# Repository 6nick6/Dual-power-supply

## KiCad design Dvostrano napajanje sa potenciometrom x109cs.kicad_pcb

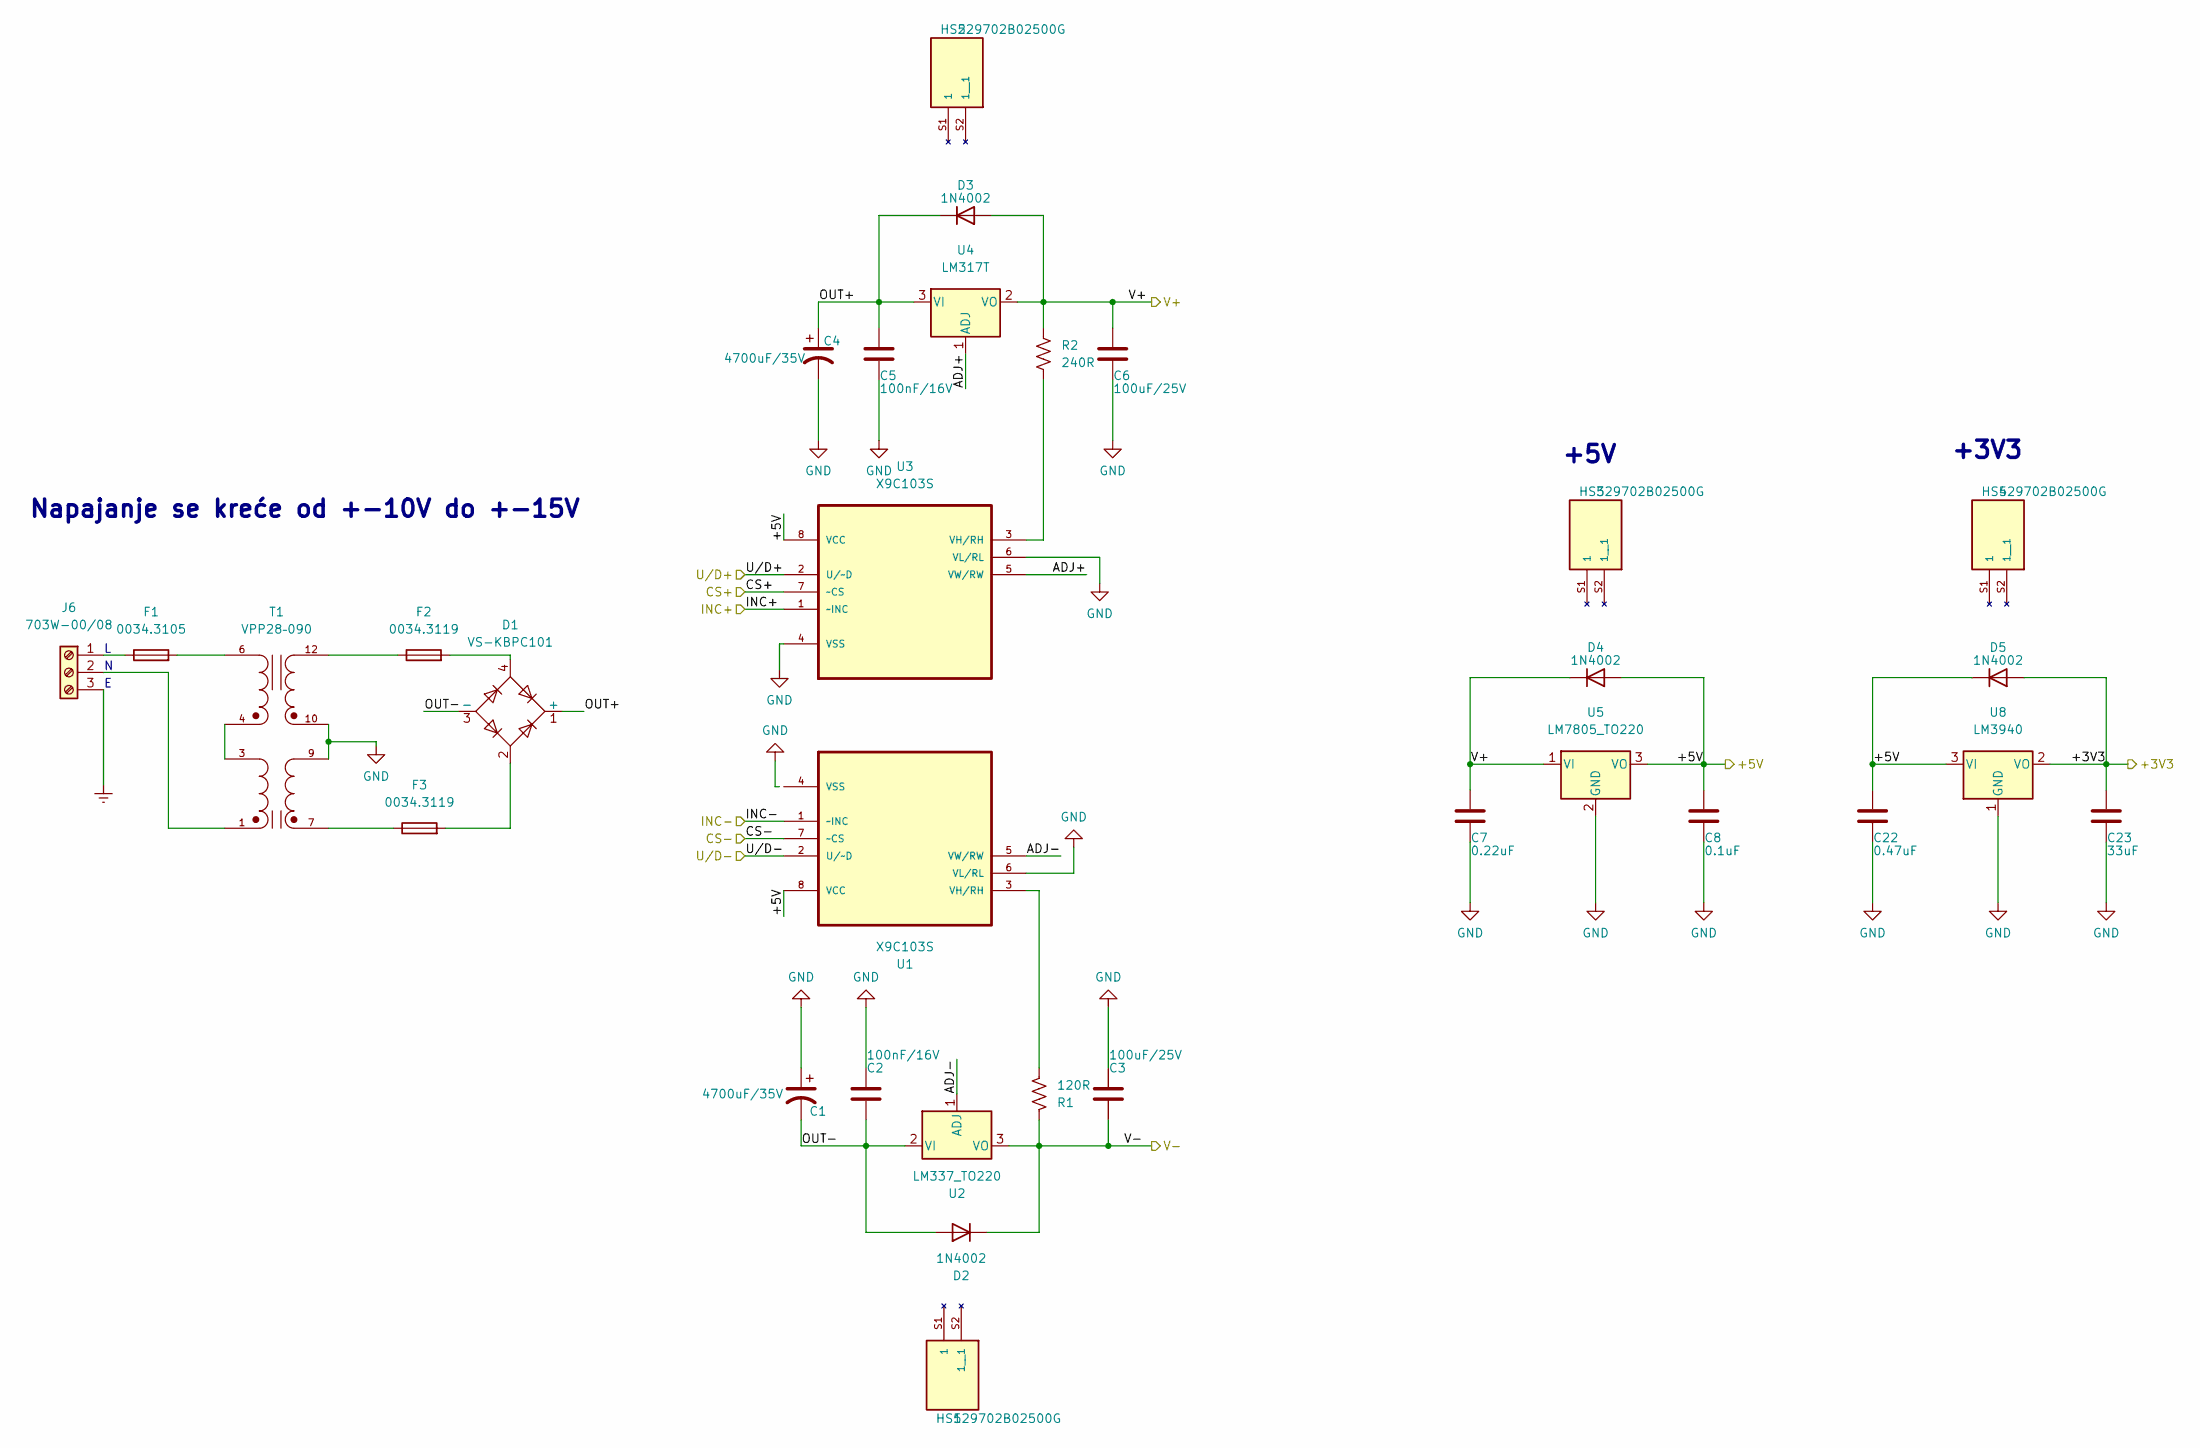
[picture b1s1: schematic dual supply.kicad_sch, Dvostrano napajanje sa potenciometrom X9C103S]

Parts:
C1, C4: 4700uF/35V; CAPPRD750W80D1800H4200
C2, C5: 100nF/16V; C_0805_2012Metric
C3, C6: 100uF/25V; C_0805_2012Metric
C7: 0.22uF; C_0805_2012Metric
C8: 0.1uF; C_0805_2012Metric
C22: 0.47uF; C_0805_2012Metric
C23: 33uF; C_0805_2012Metric
D1: VS-KBPC101; Diode_Bridge_Vishay_KBPC1
D2, D3, D4, D5: 1N4002; D_DO-41_SOD81_P10.16mm_Horizontal
F1: 0034.3105; Fuseholder_Cylinder-5x20mm_Schurter_0031_8201_Horizontal_Op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
F2, F3: 0034.3119; Fuseholder_Cylinder-5x20mm_Schurter_0031_8201_Horizontal_Op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
HS1, HS2, HS3, HS4: 529702B02500G; HSINK_529702B02500G
J6: 703W-00/08; TerminalBlock_Phoenix_MKDS-1,5-3_1x03_P5.00mm_Horizontal
R1: 120R; C_0805_2012Metric
R2: 240R; C_0805_2012Metric
T1: VPP28–090; XFMR_VPP28-090
U1, U3: X9C103S; SOIC127P600X175-8N; MPN X9C103S
U2: LM337_TO220; TO-220-3_Vertical
U4: LM317T; TO-220-3_Vertical
U5: LM7805_TO220; TO-220-3_Vertical
U8: LM3940; TO-220-3_Vertical

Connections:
/+3V3: C23.1, D5.2 (A), U8.2 (VO); also elsewhere on the board
/+5V: C8.1, C22.1, D4.2 (A), D5.1 (K), U1.8 (VCC), U3.8 (VCC), U5.3 (VO), U8.3 (VI); also elsewhere on the board
/CS+: U3.7 (~CS); also elsewhere on the board
/CS-: U1.7 (~CS); also elsewhere on the board
/Dual supply/ADJ+: U3.5 (VW/RW), U4.1 (ADJ)
/Dual supply/ADJ-: U1.5 (VW/RW), U2.1 (ADJ)
/Dual supply/OUT+: C4.1, C5.1, D1.1 (+), D3.1 (K), U4.3 (VI)
/Dual supply/OUT-: C1.2, C2.1, D1.3 (-), D2.2 (A), U2.2 (VI)
/INC+: U3.1 (~INC); also elsewhere on the board
/INC-: U1.1 (~INC); also elsewhere on the board
/U/D+: U3.2 (U/~D); also elsewhere on the board
/U/D-: U1.2 (U/~D); also elsewhere on the board
/V+: C6.1, C7.1, D3.2 (A), D4.1 (K), R2.1, U4.2 (VO), U5.1 (VI); also elsewhere on the board
/V-: C3.1, D2.1 (K), R1.1, U2.3 (VO); also elsewhere on the board
Earth: J6.3
GND: C1.1, C2.2, C3.2, C4.2, C5.2, C6.2, C7.2, C8.2, C22.2, C23.2, T1.9, T1.10, U1.6 (VL/RL), U3.4 (VSS), U3.6 (VL/RL), U5.2 (GND), U8.1 (GND); also elsewhere on the board
unnamed: D1.2, F3.2
unnamed: D1.4, F2.2
unnamed: F1.1, J6.1
unnamed: F1.2, T1.6
unnamed: F2.1, T1.12
unnamed: F3.1, T1.7
unnamed: J6.2, T1.1
unnamed: R1.2, U1.3 (VH/RH)
unnamed: R2.2, U3.3 (VH/RH)
unnamed: T1.3, T1.4

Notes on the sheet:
+3V3
+5V
Napajanje se kreće od +-10V do +-15V

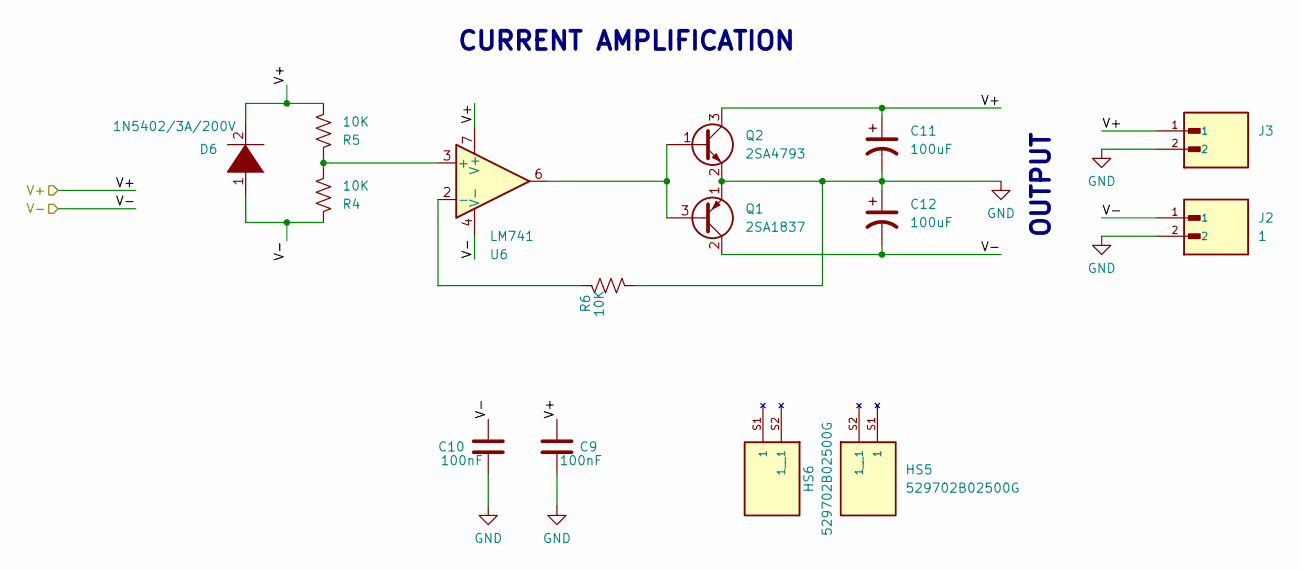
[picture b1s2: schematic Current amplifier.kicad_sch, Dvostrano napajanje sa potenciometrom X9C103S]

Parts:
C9, C10: 100nF; CAPC2012X70
C11, C12: 100uF; CP_Radial_D7.5mm_P2.50mm
D6: 1N5402/3A/200V; D_DO-201AD_P15.24mm_Horizontal
HS5, HS6: 529702B02500G; HSINK_529702B02500G
J2, J3: 1; TerminalBlock_Phoenix_MKDS-1,5-2_1x02_P5.00mm_Horizontal; PARTREV 11.03.2024
Q1: 2SA1837; TO-220-3_Vertical
Q2: 2SA4793; TO-220-3_Vertical
R4, R5, R6: 10K; R_0805_2012Metric
U6: LM741; DIP-8_W7.62mm

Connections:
/V+: C9.1, C11.1, D6.2 (A), J3.1, Q2.3 (C), R5.2, U6.7 (V+); also elsewhere on the board
/V-: C10.1, C12.2, D6.1 (K), J2.1, Q1.2 (C), R4.1, U6.4 (V-); also elsewhere on the board
GND: C9.2, C10.2, C11.2, C12.1, J2.2, J3.2, Q1.1 (E), Q2.2 (E), R6.2; also elsewhere on the board
unnamed: Q1.3 (B), Q2.1 (B), U6.6
unnamed: R4.2, R5.1, U6.3 (+)
unnamed: R6.1, U6.2 (-)

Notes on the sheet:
CURRENT AMPLIFICATION
OUTPUT

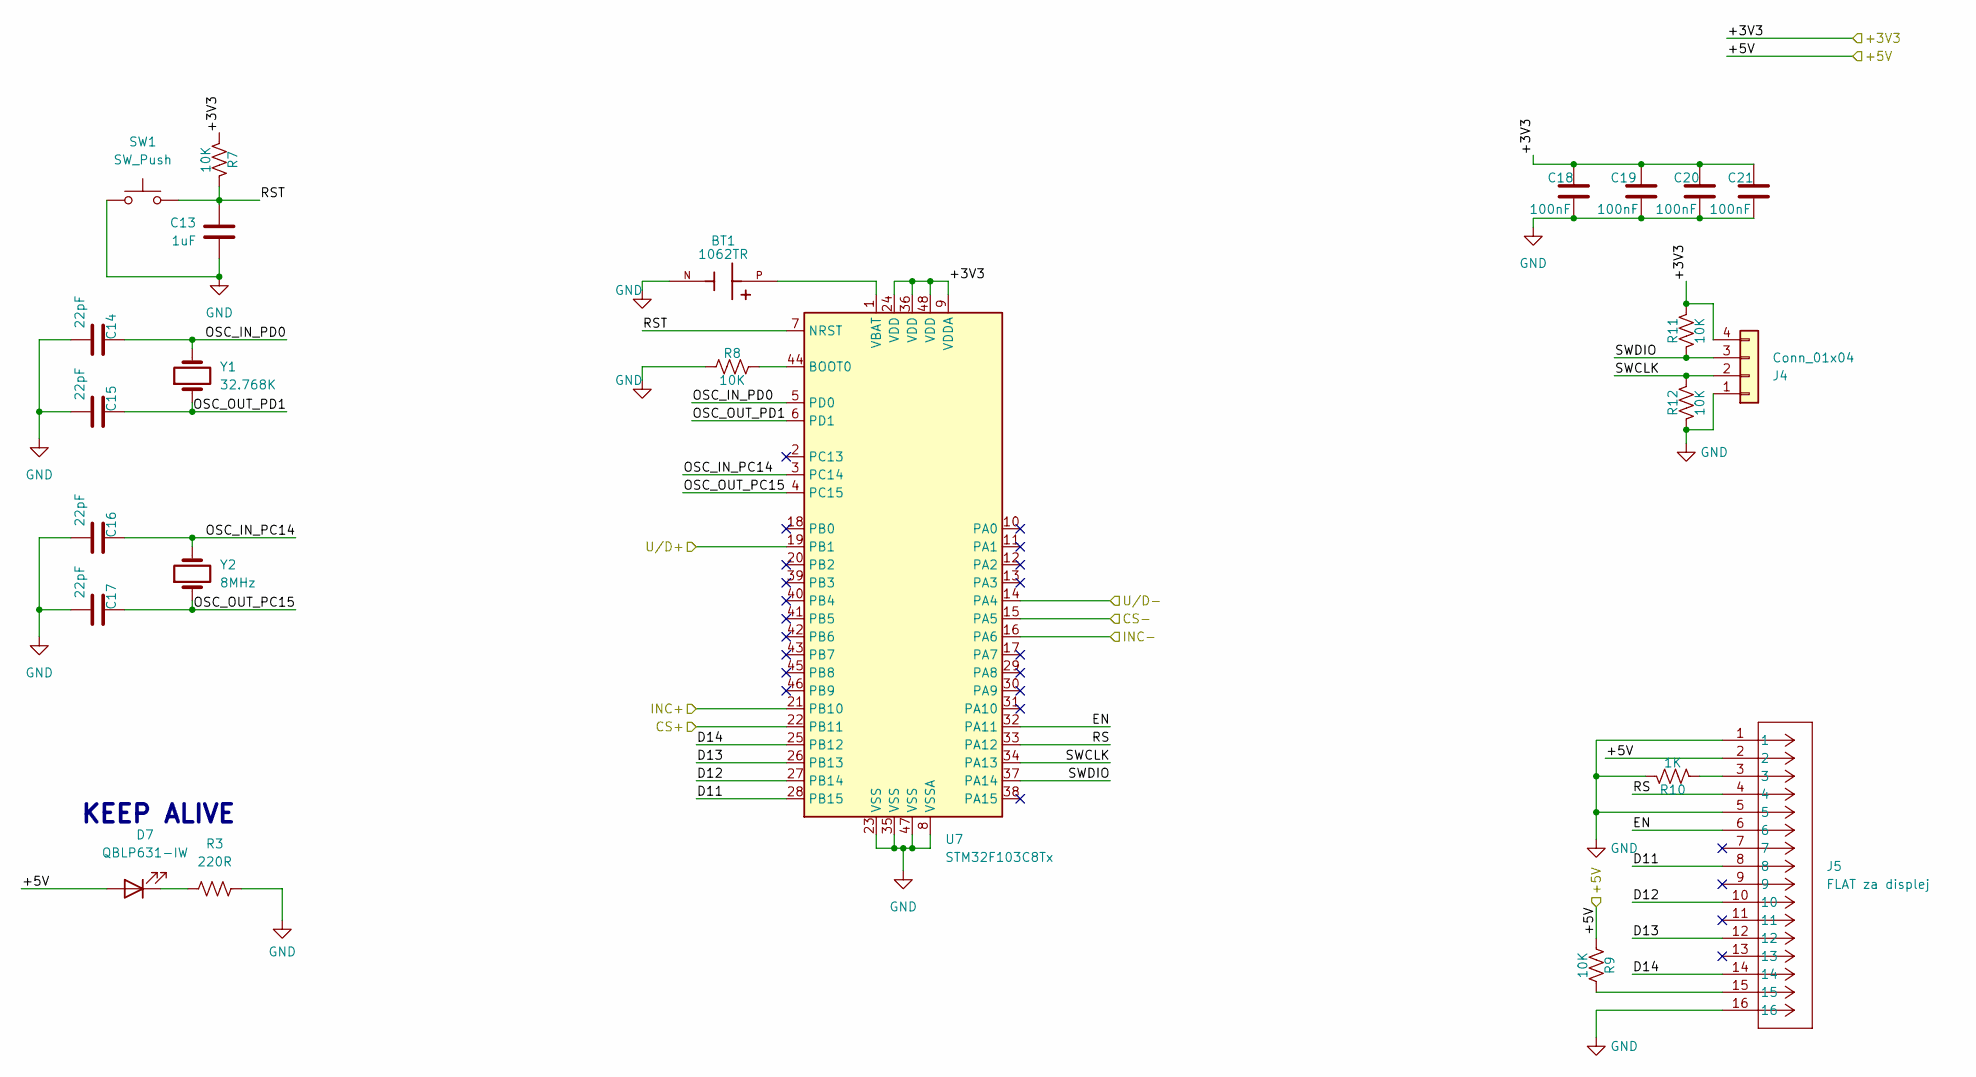
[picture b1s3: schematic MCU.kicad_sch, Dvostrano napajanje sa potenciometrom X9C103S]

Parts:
BT1: 1062TR; BAT_1062TR; PARTREV F
C13: 1uF; C_0805_2012Metric
C14, C15, C16, C17: 22pF; C_0805_2012Metric
C18, C19, C20, C21: 100nF; C_0805_2012Metric
D7: QBLP631-IW; LED_0805_2012Metric
J4: Conn_01x04; PinHeader_1x04_P2.54mm_Vertical
J5: FLAT za displej; CONN_XG4A-1631_OMR
R3: 220R; R_0805_2012Metric
R7, R8, R9, R11, R12: 10K; R_0805_2012Metric
R10: 1K; R_0805_2012Metric
SW1: SW_Push; SW_Tactile_SPST_NO_Straight_CK_PTS636Sx25SMTRLFS
U7: STM32F103C8Tx; LQFP-48_7x7mm_P0.5mm
Y1: 32.768K; Crystal_C26-LF_D2.1mm_L6.5mm_Vertical
Y2: 8MHz; Resonator-2Pin_W10.0mm_H5.0mm

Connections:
/+3V3: C18.1, C19.1, C20.1, C21.1, J4.4, R7.2, R11.1, U7.9 (VDDA), U7.24 (VDD), U7.36 (VDD), U7.48 (VDD); also elsewhere on the board
/+5V: D7.2 (A), J5.2, R9.1; also elsewhere on the board
/CS+: U7.22 (PB11); also elsewhere on the board
/CS-: U7.15 (PA5); also elsewhere on the board
/INC+: U7.21 (PB10); also elsewhere on the board
/INC-: U7.16 (PA6); also elsewhere on the board
/MCU/D11: J5.8, U7.28 (PB15)
/MCU/D12: J5.10, U7.27 (PB14)
/MCU/D13: J5.12, U7.26 (PB13)
/MCU/D14: J5.14, U7.25 (PB12)
/MCU/EN: J5.6, U7.32 (PA11)
/MCU/OSC_IN_PC14: C16.1, U7.3 (PC14), Y2.2
/MCU/OSC_IN_PD0: C14.1, U7.5 (PD0), Y1.2
/MCU/OSC_OUT_PC15: C17.1, U7.4 (PC15), Y2.1
/MCU/OSC_OUT_PD1: C15.1, U7.6 (PD1), Y1.1
/MCU/RS: J5.4, U7.33 (PA12)
/MCU/RST: C13.2, R7.1, SW1.2, U7.7 (NRST)
/MCU/SWCLK: J4.2, R12.1, U7.34 (PA13)
/MCU/SWDIO: J4.3, R11.2, U7.37 (PA14)
/U/D+: U7.19 (PB1); also elsewhere on the board
/U/D-: U7.14 (PA4); also elsewhere on the board
GND: BT1.N, C13.1, C14.2, C15.2, C16.2, C17.2, C18.2, C19.2, C20.2, C21.2, J4.1, J5.1, J5.5, J5.16, R3.2, R8.1, R10.1, R12.2, SW1.1, U7.8 (VSSA), U7.23 (VSS), U7.35 (VSS), U7.47 (VSS); also elsewhere on the board
unnamed: BT1.P, U7.1 (VBAT)
unnamed: D7.1 (K), R3.1
unnamed: J5.3, R10.2
unnamed: J5.15, R9.2
unnamed: R8.2, U7.44 (BOOT0)

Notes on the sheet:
KEEP ALIVE

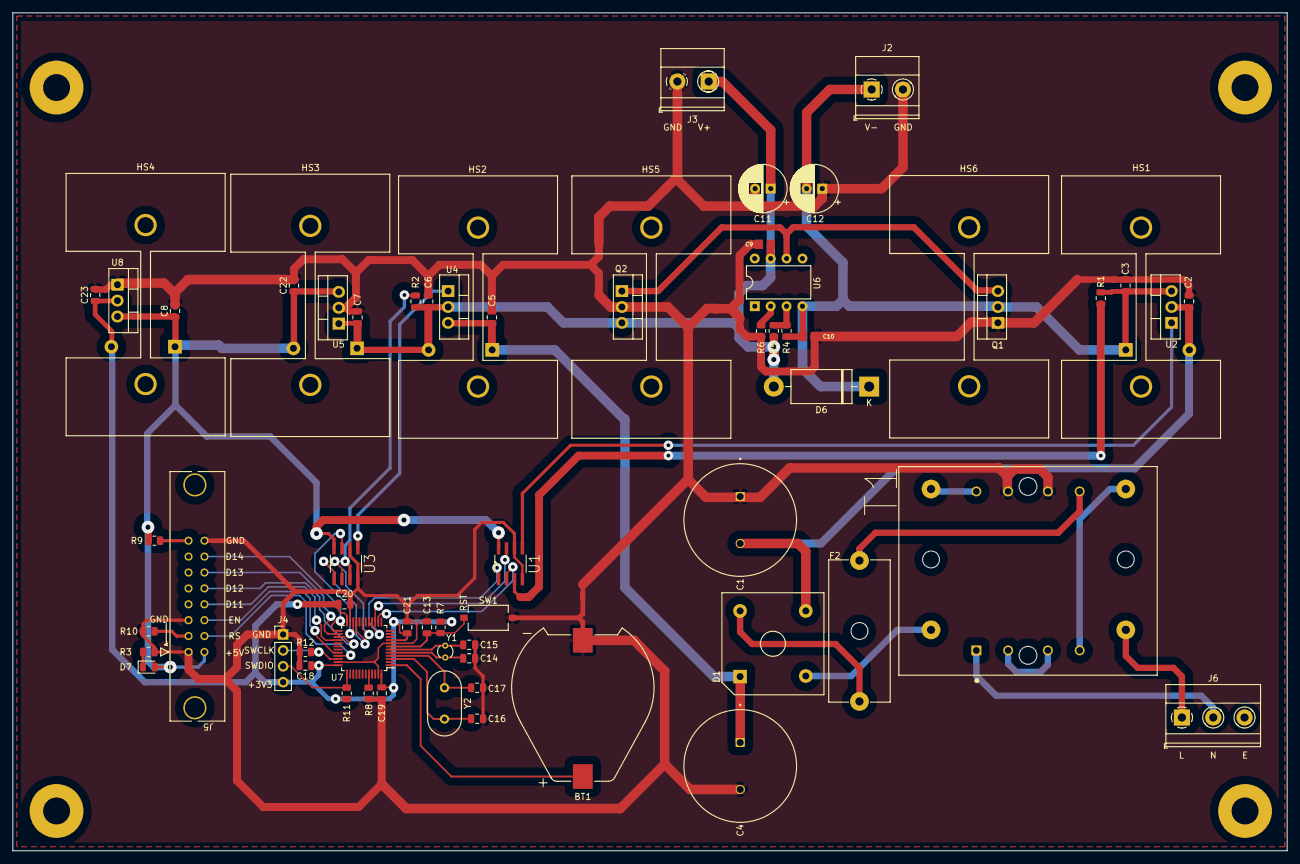
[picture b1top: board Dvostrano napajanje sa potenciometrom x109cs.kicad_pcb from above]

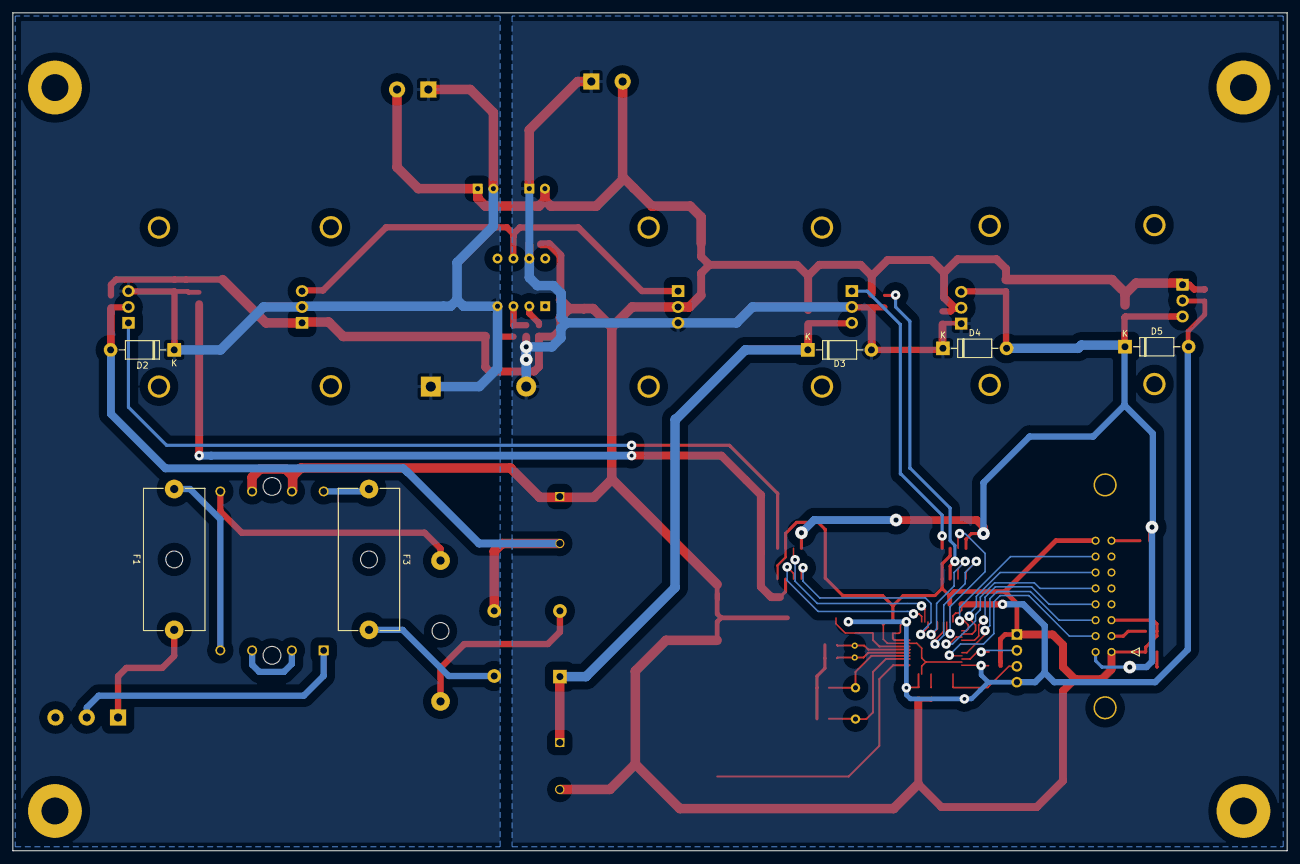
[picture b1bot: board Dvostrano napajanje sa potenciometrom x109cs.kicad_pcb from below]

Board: 2 copper layers, 203.6 x 133.9 mm, 71 parts (6 on the bottom side), 46 nets.

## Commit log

2025-07-31 Inicijalni commit KiCad projekta
2025-07-31 dodat tekst
2025-07-31 Simetricno postavljeni regulatori LM337 i LM317, labele V_- i V_+ su obrisane i digitalni potenciometri su vezani direktno za otpornike
2025-07-31 Promenjen je bypass kondenzator na LM317-T, umesto 100nF/16V sada stoji 100uF/25V.
2025-08-03 Postavljen je Switch na šematiku za mikrokontroler, takođe je povezan na PCB-u.
2025-08-28 dodat buffer
2025-08-28 Obrisan buffer
2025-08-28 proba
